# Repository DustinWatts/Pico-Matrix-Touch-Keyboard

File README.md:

# Pico-Matrix-Touch-Keyboard

A touchscreen matrix using an 3.5" ILI9488 TFT with resistive touch and a Raspberry Pi Pico. The Raspberry Pi Pico has native HID Keyboard support. This sketch gives you 12 buttons in a 4x3 matrix. Each button can have one or more keyboard functions. 

## Earle Philhower's `arduino-pico` core
Installing the `arduino-pico` (https://github.com/earlephilhower/arduino-pico) core: 

- In the Arduino IDE go to File->Preferences.
- Under "Additional Board Manager URLs" add this line:
	`https://github.com/earlephilhower/arduino-pico/releases/download/global/package_rp2040_index.json`. Click OK.
- Go to Tools->Boards->Board Manager. Type "pico" in the search box and click "Install" for "Raspberry Pi Pico/RP2040".

## Upload settings

The sketch and board have been tested with the following Board Settings:

## LittleFS
This example uses LittleFS for a tiny bit of storage. Storage is needed to store the calibration file that is created when calibrating the touchscreen. So make sure when you flash the Pico, you flash it with at least 64KB for the FS under "Flash Size".

## Pico TFT Combiner board
For better connections and a nice finished project you can use the Pico + TFT Combiner board I designed. You can order these straight from PCBWay (https://www.pcbway.com/project/shareproject/Pico_Matrix_Touch_Keypad.html), donwload the gerbers, or the Kicad project. You can find them in the `Pico_TFT_Combiner_Board` folder of this repository.

## Connections

You can use the diagrams below if you want to connect the screen without using the combiner board.

## Support Me

If you like what I am doing, there are a number of ways you can support me. 

| Platform | Link|
|:-----:|:-----|
|  | You can follow me on Twitter: [@dustinwattsnl](https://twitter.com/dustinwattsnl "Follow me on Twitter")|
|  | You can subscribe to my channel on Youtube: [/dustinWatts](https://www.youtube.com/dustinwatts "Subscribe to my YouTube channel") |
|  | You can support me by becoming a patron on Patreon: https://www.patreon.com/dustinwatts |
|  | You can make a one time donation using PayPal.me: https://www.paypal.me/dustinwattsnl |

## Get help

For quick access to help you can join my Discord server: https://discord.gg/RE3XevS

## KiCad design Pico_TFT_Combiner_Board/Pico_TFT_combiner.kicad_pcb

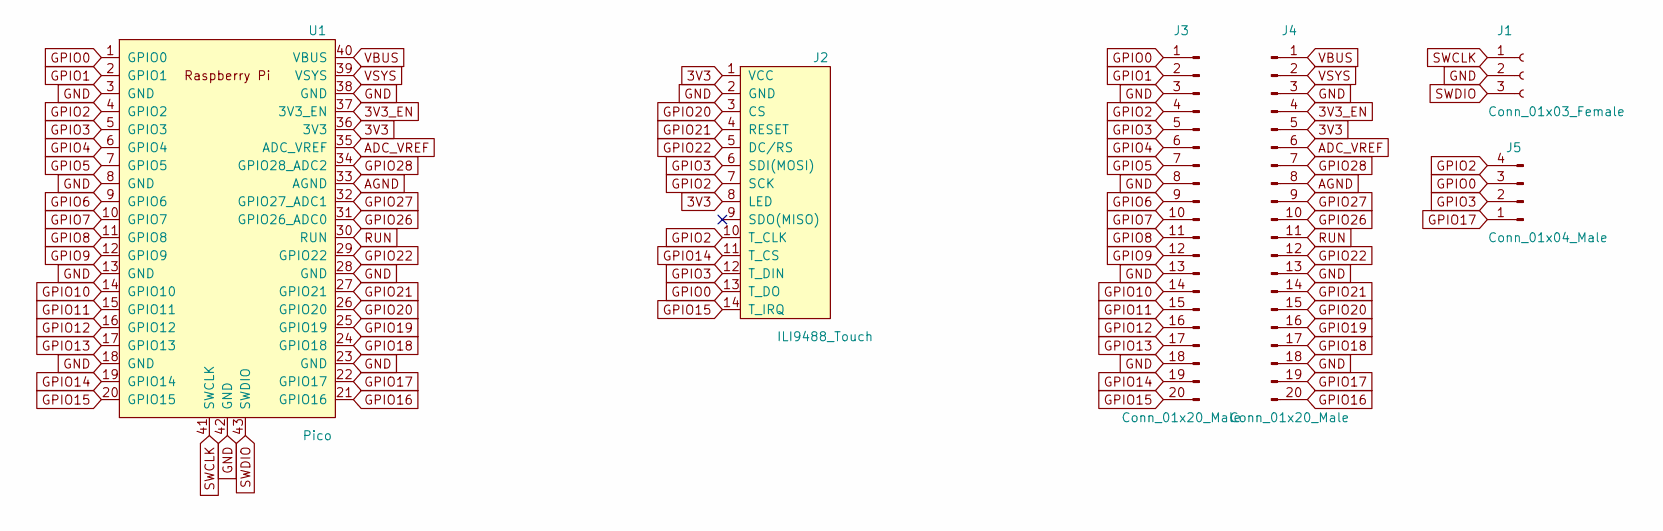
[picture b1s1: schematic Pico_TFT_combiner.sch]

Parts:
J1: Conn_01x03_Female; PinSocket_1x03_P2.54mm_Vertical
J2: ILI9488_Touch; PinHeader_1x14_P2.54mm_Vertical
J3, J4: Conn_01x20_Male; PinHeader_1x20_P2.54mm_Vertical
J5: Conn_01x04_Male; PinHeader_1x04_P2.54mm_Vertical
U1: Pico; RPi_Pico_SMD_TH

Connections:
3V3: J2.1 (VCC), J2.8 (LED), J4.5, U1.36 (3V3)
3V3_EN: J4.4, U1.37 (3V3_EN)
ADC_VREF: J4.6, U1.35 (ADC_VREF)
AGND: J4.8, U1.33 (AGND)
GND: J1.2, J2.2 (GND), J3.3, J3.8, J3.13, J3.18, J4.3, J4.13, J4.18, U1.3 (GND), U1.8 (GND), U1.13 (GND), U1.18 (GND), U1.23 (GND), U1.28 (GND), U1.38 (GND), U1.42 (GND)
GPIO0: J2.13 (T_DO), J3.1, J5.3, U1.1 (GPIO0)
GPIO1: J3.2, U1.2 (GPIO1)
GPIO2: J2.7 (SCK), J2.10 (T_CLK), J3.4, J5.4, U1.4 (GPIO2)
GPIO3: J2.6 (SDI(MOSI)), J2.12 (T_DIN), J3.5, J5.2, U1.5 (GPIO3)
GPIO4: J3.6, U1.6 (GPIO4)
GPIO5: J3.7, U1.7 (GPIO5)
GPIO6: J3.9, U1.9 (GPIO6)
GPIO7: J3.10, U1.10 (GPIO7)
GPIO8: J3.11, U1.11 (GPIO8)
GPIO9: J3.12, U1.12 (GPIO9)
GPIO10: J3.14, U1.14 (GPIO10)
GPIO11: J3.15, U1.15 (GPIO11)
GPIO12: J3.16, U1.16 (GPIO12)
GPIO13: J3.17, U1.17 (GPIO13)
GPIO14: J2.11 (T_CS), J3.19, U1.19 (GPIO14)
GPIO15: J2.14 (T_IRQ), J3.20, U1.20 (GPIO15)
GPIO16: J4.20, U1.21 (GPIO16)
GPIO17: J4.19, J5.1, U1.22 (GPIO17)
GPIO18: J4.17, U1.24 (GPIO18)
GPIO19: J4.16, U1.25 (GPIO19)
GPIO20: J2.3 (CS), J4.15, U1.26 (GPIO20)
GPIO21: J2.4 (RESET), J4.14, U1.27 (GPIO21)
GPIO22: J2.5 (DC/RS), J4.12, U1.29 (GPIO22)
GPIO26: J4.10, U1.31 (GPIO26_ADC0)
GPIO27: J4.9, U1.32 (GPIO27_ADC1)
GPIO28: J4.7, U1.34 (GPIO28_ADC2)
RUN: J4.11, U1.30 (RUN)
SWCLK: J1.1, U1.41 (SWCLK)
SWDIO: J1.3, U1.43 (SWDIO)
VBUS: J4.1, U1.40 (VBUS)
VSYS: J4.2, U1.39 (VSYS)

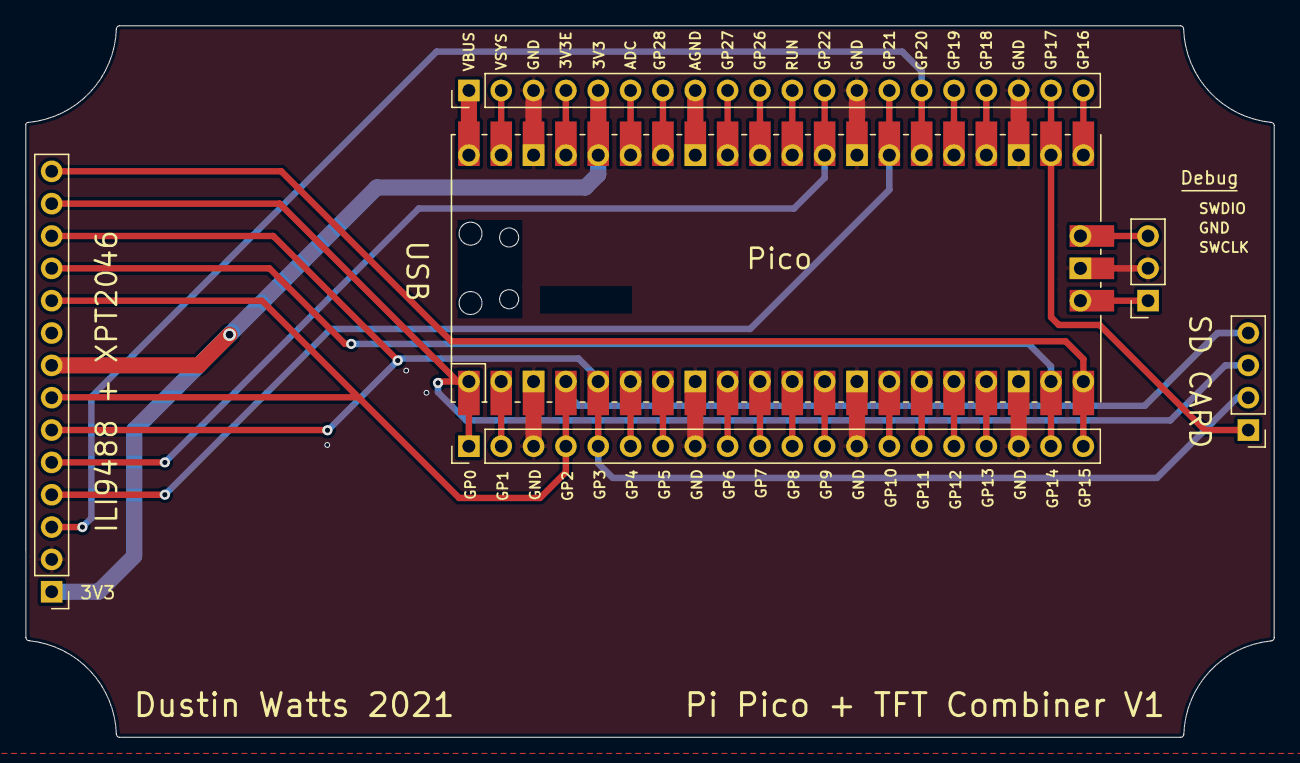
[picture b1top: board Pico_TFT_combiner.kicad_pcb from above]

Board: 2 copper layers, 98.0 x 55.9 mm, 6 parts (0 on the bottom side), 36 nets.

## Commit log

2021-05-17 Initial Commit
    Initial Commit
2021-05-18 Added combiner board gerbers
2021-05-18 Added images
2021-05-21 Added 3D models, added User_Setup.h
2021-05-23 File rename
2021-05-25 Update README, added images
2021-05-25 Update README.md
    Spelling error.
2021-05-29 Baud update, 3D model update
2021-05-29 Update schematic
2021-06-04 Update readme, better cover image
2021-06-04 Added 3D printable case
2021-06-04 Update case readme
2022-05-15 Update User_Setup.h
    SPI Frequency of 70000000 seems to be to high for the V2 screens. Changed this to 27000000 to be on the safe side for all screens.
